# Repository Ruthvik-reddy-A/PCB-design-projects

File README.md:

# 🔧 PCB Design Projects

This combined repository contains self-contained folders for each individual project, along with complete schematics, PCB layouts, documentation, and source files where applicable. It serves both as a personal portfolio and an open-source contribution to the maker and engineering community.

---

## 📁 Projects Overview

### 1. [📦 Breadboard Power Supply](./Breadboard-Power-Supply)

A compact, dual-voltage regulated power supply designed to power breadboard circuits. Ideal for prototyping and educational use.

**Key Features:**
- Outputs: 3.3V and 5V regulated
- Power input via USB or 9V barrel jack
- On/off toggle switches and status LEDs

---

### 2. [📦 MCU Datalogger with Built-in 512K EEPROM](./MCU-Datalogger-With-Built-In-512K-EEPROM)

A microcontroller-based data logger that logs sensor or serial data to a 512KB external EEPROM.

**Key Features:**
- ATmega328P-based MCU
- I²C EEPROM (24LC512)
- Power supply filtering and decoupling
- Compatible with UART, I²C sensors or serial interfaces

---

### 3. [📦 Tiny Solar Power Supply](./Tiny-Solar-Power-Supply)

A miniature solar energy harvesting module capable of charging a Li-ion battery and regulating output to power IoT devices or small loads.

**Key Features:**
- Solar input with MPPT (if supported by controller)
- Li-ion battery charging via TP4056
- Regulated 3.3V/5V output
- Compact PCB layout

---

### 4. [📦 LED Torch](./LED%20Torch)  
A compact, battery-powered LED torch circuit using minimal components. Designed for efficiency, simplicity, and portability, this project is ideal for learning basic electronics or building a low-cost flashlight.

---

### 5. [📡 GPS + GSM Tracker with EEPROM Logging](https://github.com/Ruthvik-reddy-A/PCB-design-projects/tree/main/GPS%20%2B%20GSM%20Tracker%20with%20EEPROM%20Logging)
A compact, ESP32-S3-based IoT tracker that logs GPS data locally and transmits position via GSM. Ideal for asset tracking, vehicle monitoring, and offline location logging in remote or mobile environments.

**Key Features:**
- Microcontroller: ESP32-S3-WROOM-1 with Wi-Fi + BLE
- GPS Module: NEO-8Q for real-time latitude/longitude tracking
- GSM Module: SIM800C for SMS or GPRS-based data transmission
- EEPROM: I²C-based 24LC256 for offline GPS data logging

**Power Supply:**
- Input: 3.7V LiPo battery
- Charging: TP4056 module with battery protection
- Regulation: AMS1117-3.3 for ESP32, Boost converter for SIM800C

**Communication:**
- 3× UARTs for GPS, GSM, and FTDI debugging
- 1× I²C for EEPROM and future expansion
- SPI pins available for SD card or display

**Indicators:**
- LED status for power, charging, and ESP32 boot
- Power control switch for full system on/off

---

## 📦 Folder Structure

Each folder includes:
- ✅ `README.md`
- ✅ `.gitignore`
- ✅ Schematics, PCB Layouts
- ✅ Bill of Materials (BOM)
- ✅ Gerber & Drill files
- ✅ Source code (if applicable)

---

## 🙌 Contributions

Feel free to fork or suggest improvements. Each project is self-contained and documented to allow easy reuse or remixing.

---

## 🔗 Related Repositories (Now Archived/Private)

These projects were originally developed in individual repositories:
- `PCB--BB-PowerSupply`
- `PCB--MCU-Datalogger`
- `PCB--Tiny-Solar-Power-Supply`

They have been combined here for easier access and long-term maintenance.

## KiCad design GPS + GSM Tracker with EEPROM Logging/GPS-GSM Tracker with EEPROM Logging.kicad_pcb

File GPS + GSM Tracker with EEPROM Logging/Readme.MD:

# 📡 IoT GPS-GSM Tracker with ESP32-S3 + EEPROM Logging

An ESP32-S3 based IoT hardware project for **location tracking** using a **GPS module (NEO-8Q)**, with real-time updates via **GSM (SIM800C)** and local data logging using an **I²C EEPROM (AT24C256)**. Power is managed via a **3.7V LiPo battery**, **TP4056 charger**, and **MT3608 boost converter**.

---

## 🧩 Features

- 📍 Real-time GPS tracking (NEO-8Q)
- 📡 GSM-based data transmission (SIM800C)
- 📦 EEPROM logging (AT24C256) for offline storage
- 🔋 Battery-powered with charging via TP4056
- ⚡ Boost conversion to 4.1V using MT3608
- 🧠 Controlled by ESP32-S3 (WROOM-1)

---

## 🔋 Power Architecture

| Source         | Voltage | Connected To     |
|----------------|---------|------------------|
| 3.7V LiPo      | 3.0–4.2V | TP4056 + MT3608  |
| TP4056 OUT     | 3.7V     | MT3608 Input     |
| MT3608 OUT     | 4.1V     | SIM800C VBAT     |
| LDO Regulator  | 3.3V     | ESP32, EEPROM, GPS |

---

## 🔌 Module Connections

### ESP32-S3 ↔ GPS (NEO-8Q)
| ESP32 Pin | GPS Pin |
|-----------|---------|
| RX2       | TX      |
| TX2       | RX      |
| 3.3V      | VCC     |
| GND       | GND     |

### ESP32-S3 ↔ SIM800C (via TXS0108E level shifter)
| ESP32 Pin | SIM800C Pin |
|-----------|-------------|
| TX1       | RX          |
| RX1       | TX          |
| GND       | GND         |
| OE (TXS)  | 3.3V        |

### ESP32-S3 ↔ EEPROM (AT24C256)
| ESP32 Pin | EEPROM Pin |
|-----------|-------------|
| GPIO21    | SDA         |
| GPIO22    | SCL         |
| 3.3V      | VCC         |
| GND       | GND         |

---

## 📐 Schematic Overview

📎 The following components are included:
- ESP32-S3-WROOM-1
- NEO-8Q GPS module (passive antenna)
- SIM800C GSM module with SMA antenna
- MT3608 boost converter
- TP4056 LiPo charger module
- AT24C256 EEPROM (I²C)
- Status LEDs and EN/BOOT buttons

📷 *[Include schematic image or KiCad 3D render here]*

---

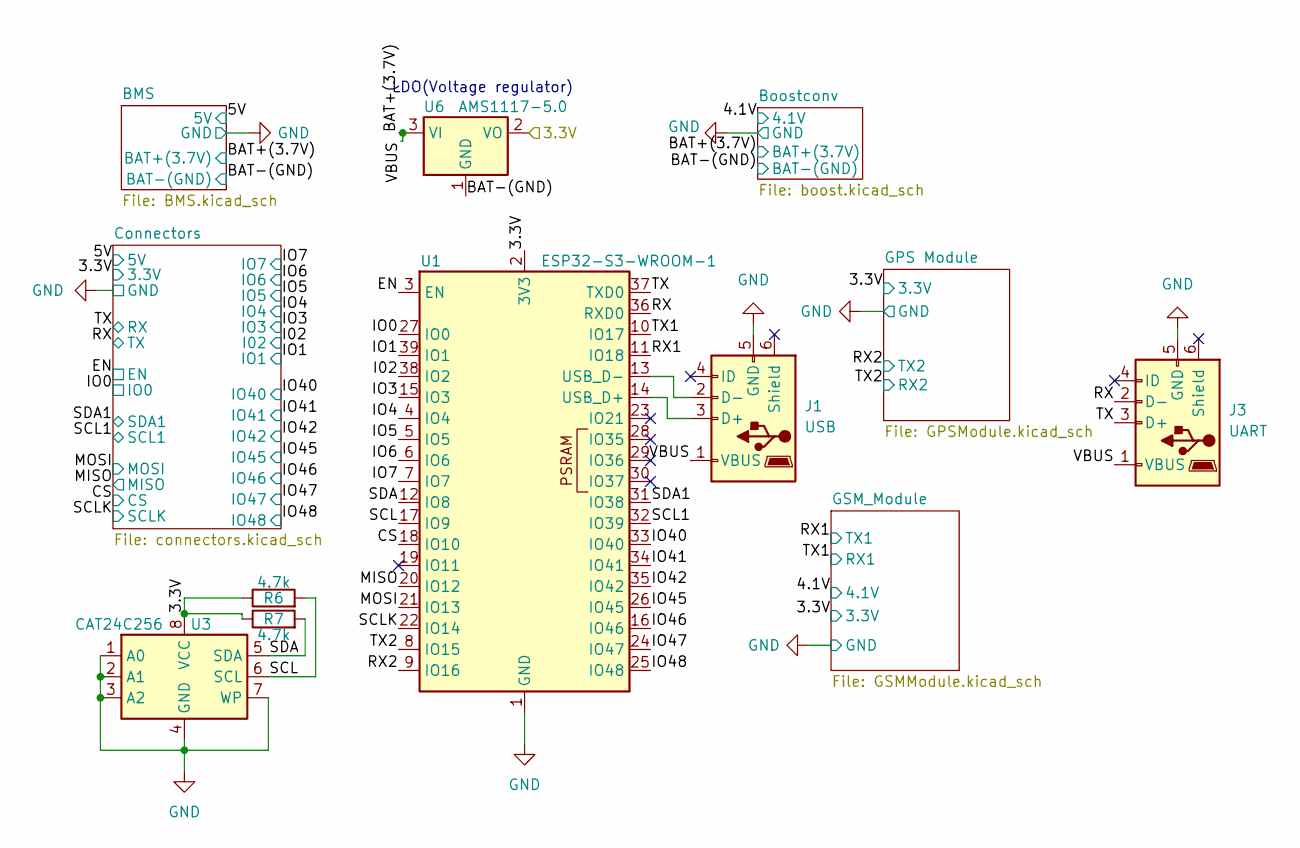
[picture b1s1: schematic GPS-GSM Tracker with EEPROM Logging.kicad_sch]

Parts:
J1: USB; USB_Micro-AB_Molex_47590-0001
J3: UART; USB_Micro-AB_Molex_47590-0001
R6, R7: 4.7k; R_0805_2012Metric
U1: ESP32-S3-WROOM-1
U3: CAT24C256; SOIC-8_3.9x4.9mm_P1.27mm
U6: AMS1117-5.0; SOT-223-3_TabPin2

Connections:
/3.3V: R6.1, R7.1, U1.2 (3V3), U3.8 (VCC), U6.2 (VO); also elsewhere on the board
/BAT+(3.7V): J1.1 (VBUS), J3.1 (VBUS), U6.3 (VI); also elsewhere on the board
/CS: U1.18 (IO10); also elsewhere on the board
/EN: U1.3 (EN); also elsewhere on the board
/I02: U1.38 (IO2); also elsewhere on the board
/IO0: U1.27 (IO0); also elsewhere on the board
/IO1: U1.39 (IO1); also elsewhere on the board
/IO3: U1.15 (IO3); also elsewhere on the board
/IO4: U1.4 (IO4); also elsewhere on the board
/IO5: U1.5 (IO5); also elsewhere on the board
/IO6: U1.6 (IO6); also elsewhere on the board
/IO7: U1.7 (IO7); also elsewhere on the board
/IO40: U1.33 (IO40); also elsewhere on the board
/IO41: U1.34 (IO41); also elsewhere on the board
/IO42: U1.35 (IO42); also elsewhere on the board
/IO45: U1.26 (IO45); also elsewhere on the board
/IO46: U1.16 (IO46); also elsewhere on the board
/IO47: U1.24 (IO47); also elsewhere on the board
/IO48: U1.25 (IO48); also elsewhere on the board
/MISO: U1.20 (IO12); also elsewhere on the board
/MOSI: U1.21 (IO13); also elsewhere on the board
/RX: J3.2 (D-), U1.36 (RXD0); also elsewhere on the board
/RX1: U1.11 (IO18); also elsewhere on the board
/RX2: U1.9 (IO16); also elsewhere on the board
/SCL: R6.2, U1.17 (IO9), U3.6 (SCL)
/SCL1: U1.32 (IO39); also elsewhere on the board
/SCLK: U1.22 (IO14); also elsewhere on the board
/SDA: R7.2, U1.12 (IO8), U3.5 (SDA)
/SDA1: U1.31 (IO38); also elsewhere on the board
/TX: J3.3 (D+), U1.37 (TXD0); also elsewhere on the board
/TX1: U1.10 (IO17); also elsewhere on the board
/TX2: U1.8 (IO15); also elsewhere on the board
GND: J1.5 (GND), J3.5 (GND), U1.1 (GND), U1.40 (GND), U1.41 (GND), U3.1 (A0), U3.2 (A1), U3.3 (A2), U3.4 (GND), U3.7 (WP), U6.1 (GND); also elsewhere on the board
unnamed 41: J1.3 (D+), U1.14 (USB_D+); also elsewhere on the board
unnamed 42: J1.2 (D-), U1.13 (USB_D-); also elsewhere on the board

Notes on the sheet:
LDO(Voltage regulator)

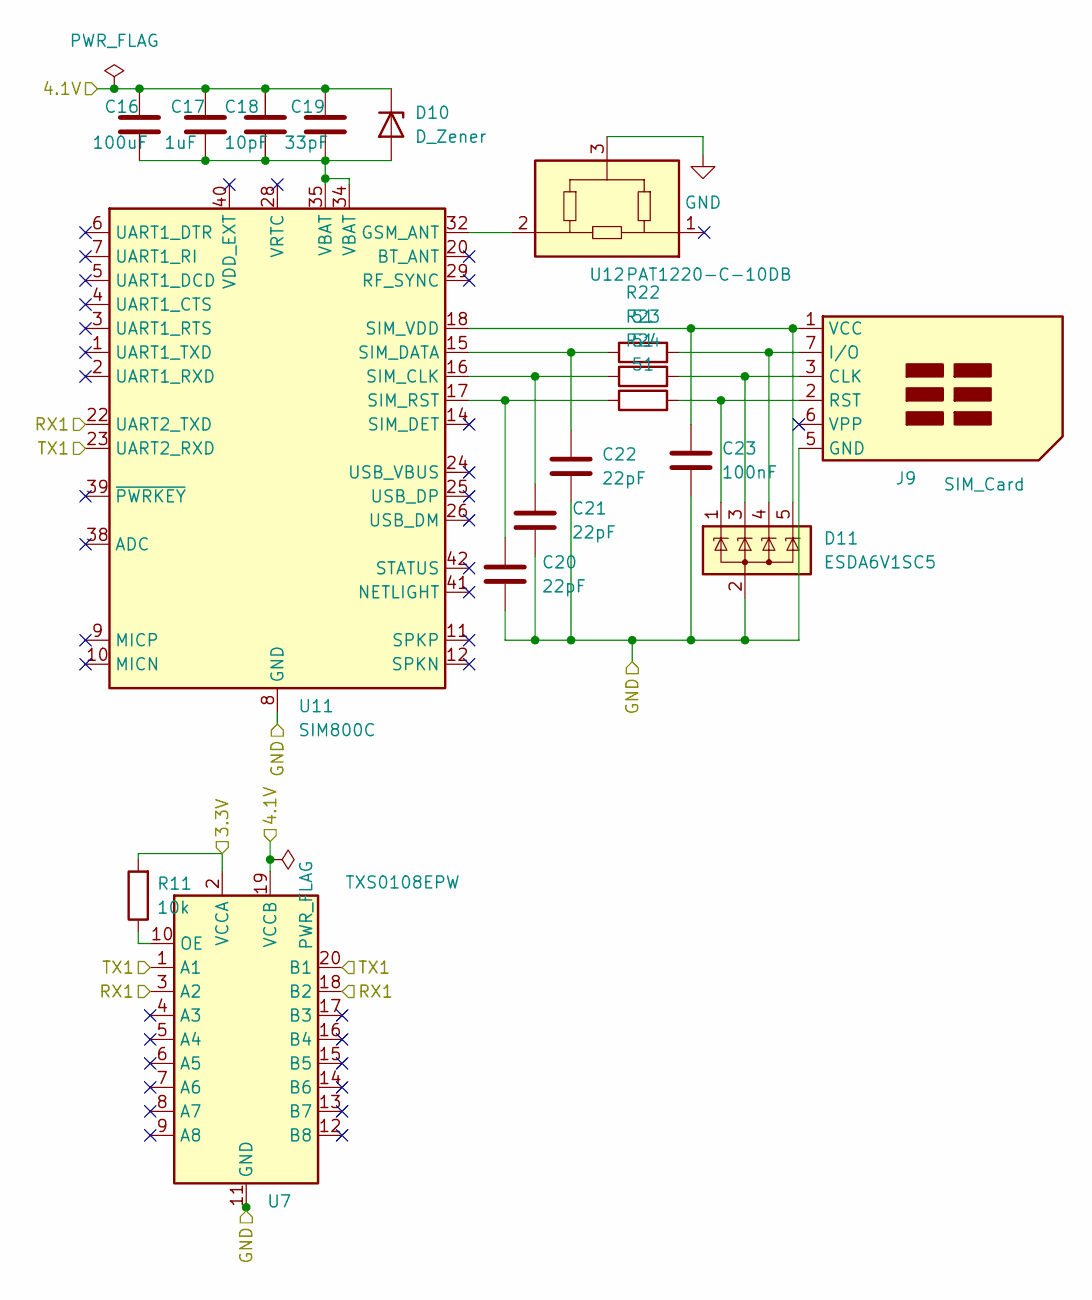
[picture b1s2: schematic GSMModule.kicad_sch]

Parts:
C16: 100uF; C_0805_2012Metric
C17: 1uF; C_0805_2012Metric
C18: 10pF; C_0805_2012Metric
C19: 33pF; C_0805_2012Metric
C20, C21, C22: 22pF; C_0805_2012Metric
C23: 100nF; C_0805_2012Metric
D10: D_Zener; D_SOD-323F
D11: ESDA6V1SC5; SOT-23-5
J9: SIM_Card; nanoSIM_GCT_SIM8060-6-0-14-00
R11: 10k; R_0805_2012Metric
R22, R23, R24: 51; R_0805_2012Metric
U7: TXS0108EPW; TSSOP-20_4.4x6.5mm_P0.65mm
U11: SIM800C; SIMCom_SIM800C
U12: PAT1220-C-10DB; RF_Attenuator_Susumu_PAT1220

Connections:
/3.3V: R11.2, U7.2 (VCCA); also elsewhere on the board
/RX1: U7.1 (A1), U7.20 (B1), U11.23 (UART2_RXD); also elsewhere on the board
/TX1: U7.3 (A2), U7.18 (B2), U11.22 (UART2_TXD); also elsewhere on the board
GND: C20.2, C21.2, C22.2, C23.2, D11.2 (A), J9.5 (GND), U7.11 (GND), U11.8 (GND), U11.13 (GND), U11.19 (GND), U11.21 (GND), U11.27 (GND), U11.30 (GND), U11.31 (GND), U11.33 (GND), U11.36 (GND), U11.37 (GND), U12.3; also elsewhere on the board
unnamed: C16.2, C17.2, C18.2, C19.2, D10.2 (A), U11.34 (VBAT), U11.35 (VBAT)
unnamed: D11.3 (K), J9.3 (CLK), R23.2
unnamed: D11.4 (K), J9.7 (I/O), R22.2
unnamed: D11.1 (K), J9.2 (RST), R24.2
unnamed: C23.1, D11.5 (K), J9.1 (VCC), U11.18 (SIM_VDD)
unnamed: R11.1, U7.10 (OE)
unnamed: U11.32 (GSM_ANT), U12.2
unnamed: C21.1, R23.1, U11.16 (SIM_CLK)
unnamed: C22.1, R22.1, U11.15 (SIM_DATA)
unnamed: C20.1, R24.1, U11.17 (SIM_RST)
PWR_FLAG: C16.1, C17.1, C18.1, C19.1, D10.1 (K), U7.19 (VCCB); also elsewhere on the board

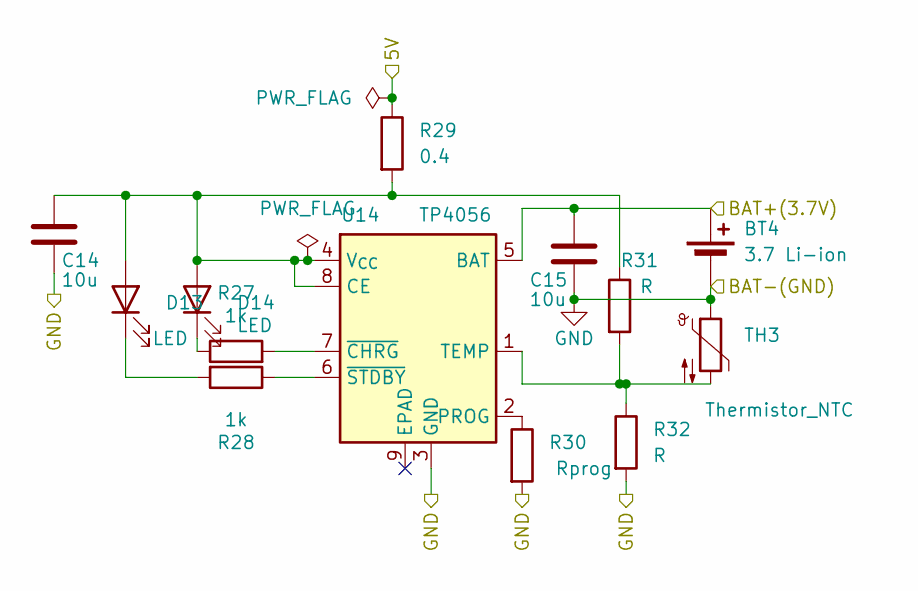
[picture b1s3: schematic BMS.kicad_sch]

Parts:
BT4: 3.7 Li-ion; BatteryHolder_Keystone_1042_1x18650
C14, C15: 10u; C_0805_2012Metric
D13, D14: LED; LED_0805_2012Metric
R27, R28: 1k; R_0805_2012Metric
R29: 0.4; R_0805_2012Metric
R30: Rprog; R_0805_2012Metric
R31, R32: R; R_0805_2012Metric
TH3: Thermistor_NTC; Heraeus_TO-92-2
U14: TP4056; SOIC-8-1EP_3.9x4.9mm_P1.27mm_EP2.41x3.3mm_ThermalVias

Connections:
/5V: R29.1; also elsewhere on the board
/BAT+(3.7V): BT4.1 (+), C15.1, U14.5 (BAT); also elsewhere on the board
GND: BT4.2 (-), C14.2, C15.2, R30.2, R32.2, TH3.1, U14.3 (GND); also elsewhere on the board
unnamed: C14.1, D13.2 (A), D14.2 (A), R29.2, R31.1, U14.4 (V_{CC}), U14.8 (CE)
unnamed: D13.1 (K), R28.2
unnamed: D14.1 (K), R27.1
unnamed: R30.1, U14.2 (PROG)
unnamed: R31.2, R32.1, TH3.2, U14.1 (TEMP)
unnamed: R27.2, U14.7 (~CHRG)
unnamed: R28.1, U14.6 (~STDBY)

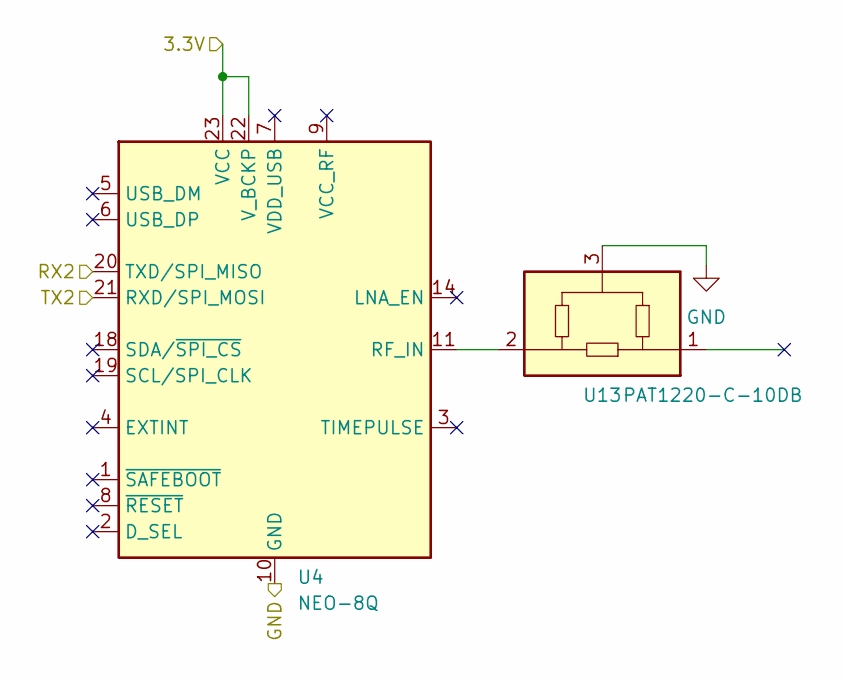
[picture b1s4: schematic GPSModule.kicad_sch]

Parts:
U4: NEO-8Q; ublox_NEO
U13: PAT1220-C-10DB; RF_Attenuator_Susumu_PAT1220

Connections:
/3.3V: U4.22 (V_BCKP), U4.23 (VCC); also elsewhere on the board
/RX2: U4.21 (RXD/SPI_MOSI); also elsewhere on the board
/TX2: U4.20 (TXD/SPI_MISO); also elsewhere on the board
GND: U4.10 (GND), U4.12 (GND), U4.13 (GND), U4.24 (GND), U13.3; also elsewhere on the board
unnamed: U4.11 (RF_IN), U13.2

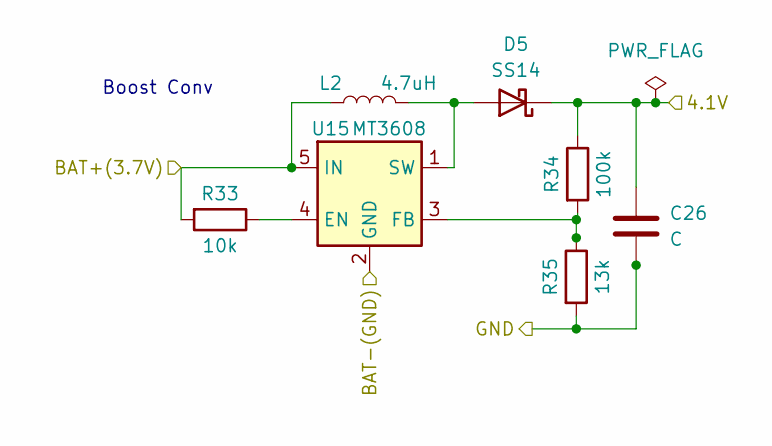
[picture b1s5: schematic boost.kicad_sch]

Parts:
C26: C; C_0805_2012Metric
D5: SS14; D_SMA
L2: 4.7uH; L_0805_2012Metric
R33: 10k; R_0805_2012Metric
R34: 100k; R_0805_2012Metric
R35: 13k; R_0805_2012Metric
U15: MT3608; SOT-23-6

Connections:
/BAT+(3.7V): L2.1, R33.2, U15.5 (IN); also elsewhere on the board
GND: C26.1, R35.2, U15.2 (GND); also elsewhere on the board
unnamed: D5.2 (A), L2.2, U15.1 (SW)
unnamed: R33.1, U15.4 (EN)
unnamed: R34.2, R35.1, U15.3 (FB)
PWR_FLAG: C26.2, D5.1 (K), R34.1; also elsewhere on the board

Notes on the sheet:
Boost Conv

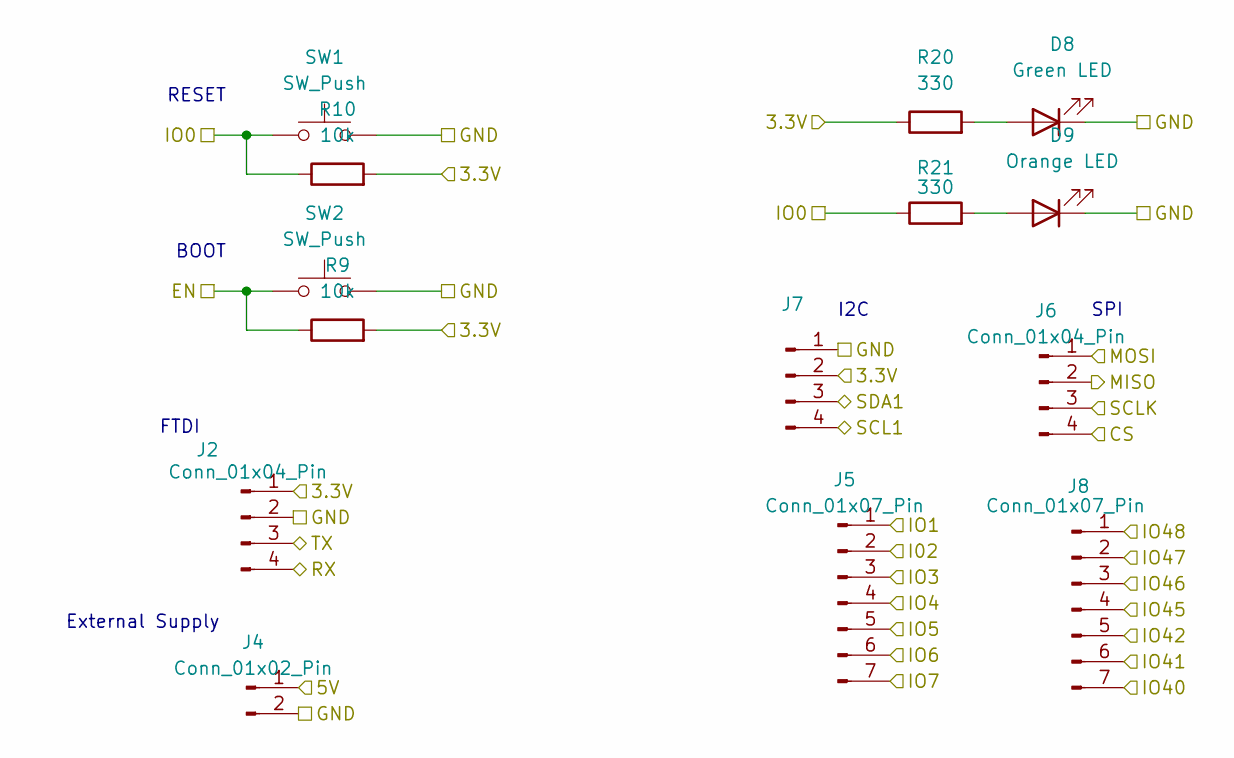
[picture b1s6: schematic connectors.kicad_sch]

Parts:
D8: Green LED; LED_0805_2012Metric
D9: Orange LED; LED_0805_2012Metric
J2, J6, J7: Conn_01x04_Pin; Molex_KK-254_AE-6410-04A_1x04_P2.54mm_Vertical
J4: Conn_01x02_Pin; Molex_KK-254_AE-6410-02A_1x02_P2.54mm_Vertical
J5, J8: Conn_01x07_Pin; Molex_KK-254_AE-6410-07A_1x07_P2.54mm_Vertical
R9, R10: 10k; R_0805_2012Metric
R20, R21: 330; R_0805_2012Metric
SW1, SW2: SW_Push; SW_PUSH_6mm_H4.3mm

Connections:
/3.3V: J2.1, J7.2, R9.2, R10.2, R20.1; also elsewhere on the board
/5V: J4.1; also elsewhere on the board
/CS: J6.4; also elsewhere on the board
/EN: R9.1, SW2.1; also elsewhere on the board
/I02: J5.2; also elsewhere on the board
/IO0: R10.1, R21.1, SW1.1; also elsewhere on the board
/IO1: J5.1; also elsewhere on the board
/IO3: J5.3; also elsewhere on the board
/IO4: J5.4; also elsewhere on the board
/IO5: J5.5; also elsewhere on the board
/IO6: J5.6; also elsewhere on the board
/IO7: J5.7; also elsewhere on the board
/IO40: J8.7; also elsewhere on the board
/IO41: J8.6; also elsewhere on the board
/IO42: J8.5; also elsewhere on the board
/IO45: J8.4; also elsewhere on the board
/IO46: J8.3; also elsewhere on the board
/IO47: J8.2; also elsewhere on the board
/IO48: J8.1; also elsewhere on the board
/MISO: J6.2; also elsewhere on the board
/MOSI: J6.1; also elsewhere on the board
/RX: J2.3; also elsewhere on the board
/SCL1: J7.4; also elsewhere on the board
/SCLK: J6.3; also elsewhere on the board
/SDA1: J7.3; also elsewhere on the board
/TX: J2.4; also elsewhere on the board
GND: D8.1 (K), D9.1 (K), J2.2, J4.2, J7.1, SW1.2, SW2.2; also elsewhere on the board
unnamed: D8.2 (A), R20.2
unnamed: D9.2 (A), R21.2

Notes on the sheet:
External Supply
I2C
FTDI
BOOT
SPI
RESET

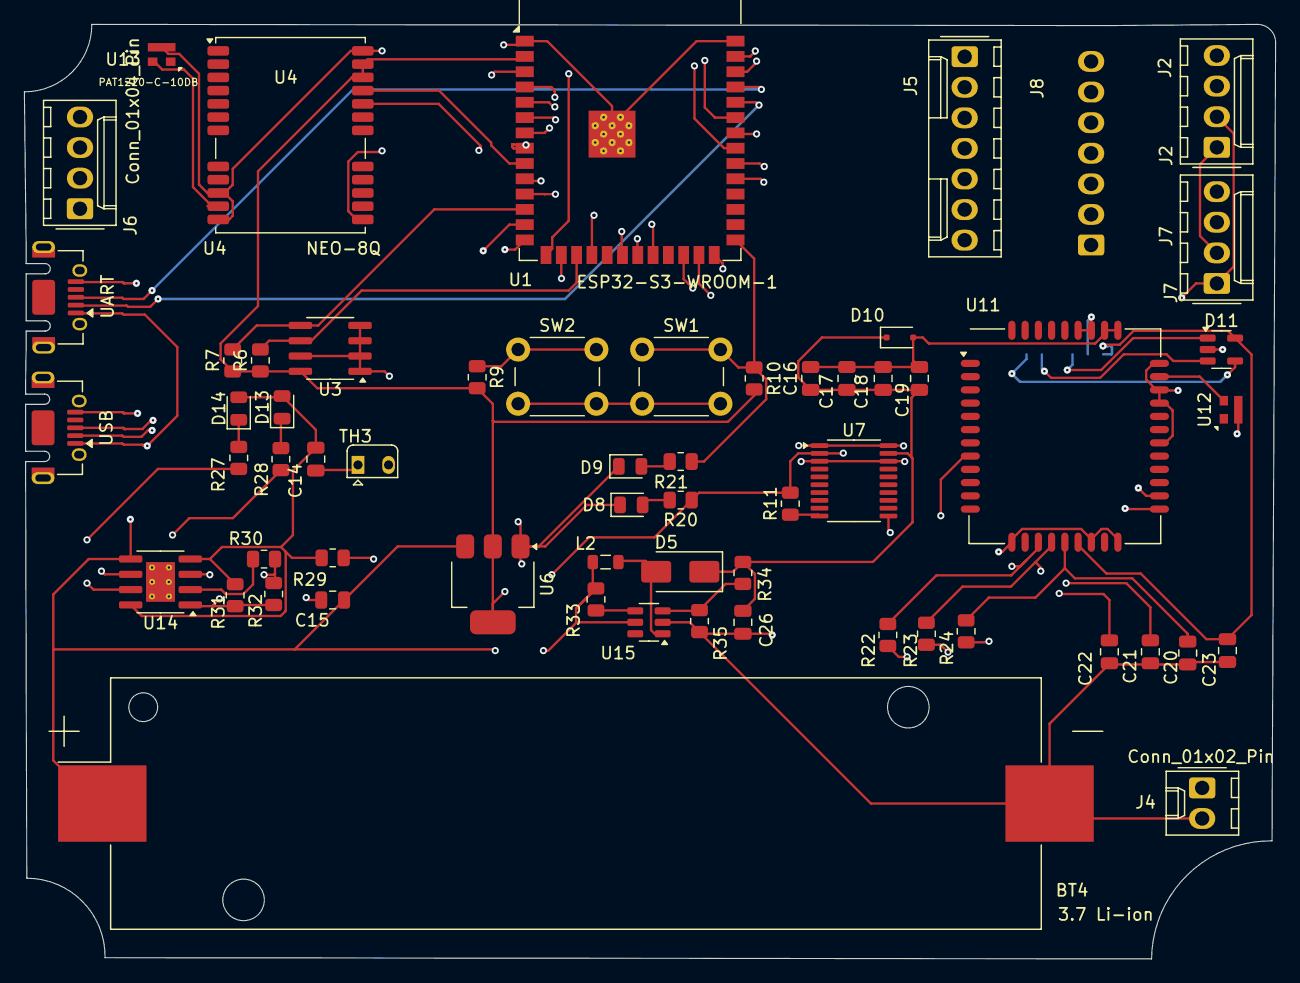
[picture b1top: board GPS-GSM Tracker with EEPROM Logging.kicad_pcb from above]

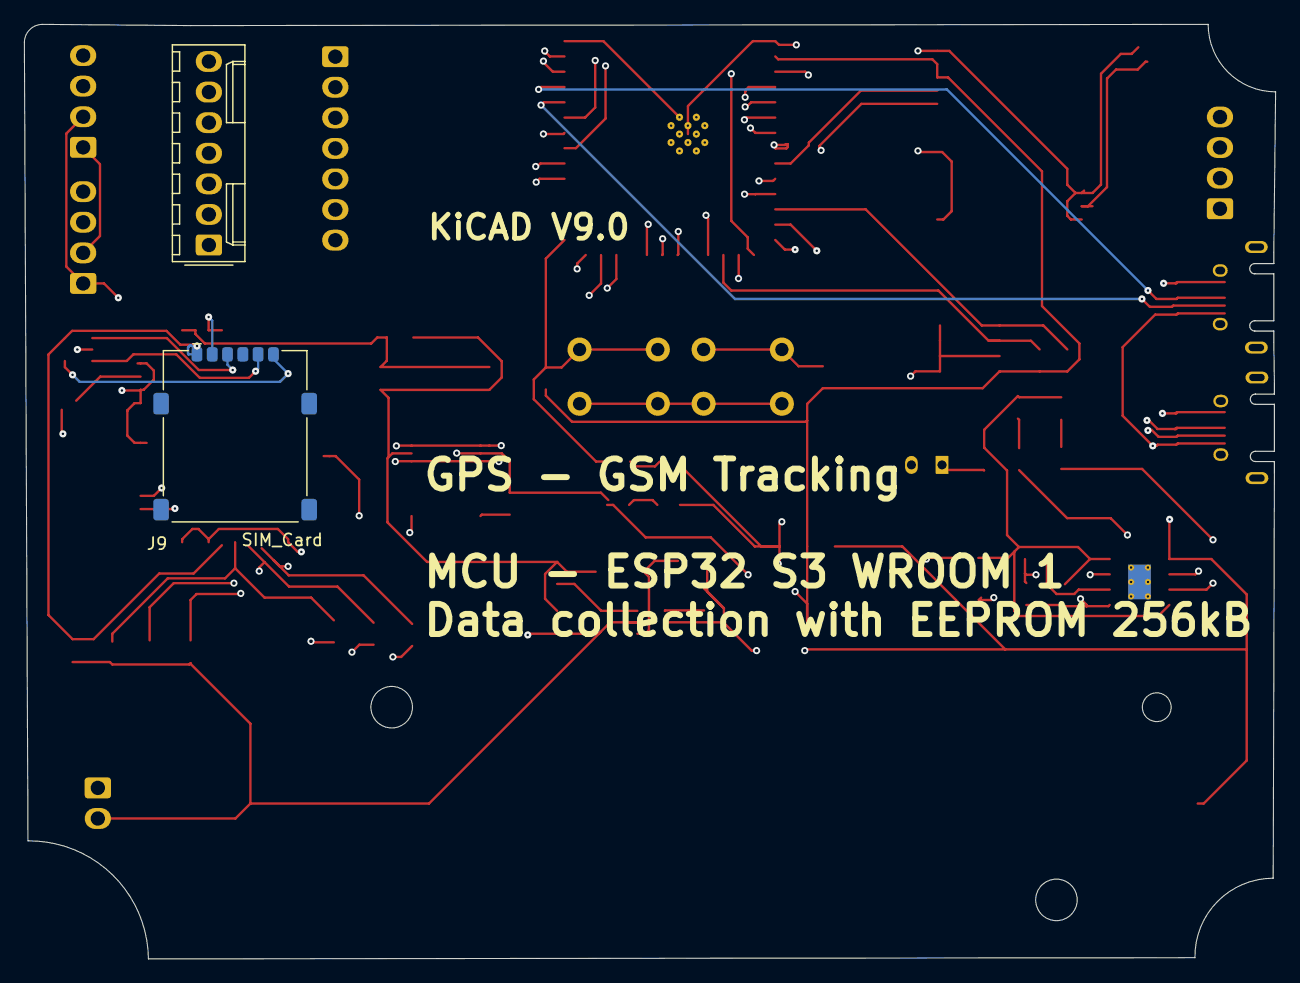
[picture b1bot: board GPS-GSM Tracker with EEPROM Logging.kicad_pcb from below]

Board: 4 copper layers, 103.9 x 77.6 mm, 61 parts (2 on the bottom side), 60 nets.

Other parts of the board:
UART: UART; USB_Micro-AB_Molex_47590-0001
USB: USB; USB_Micro-AB_Molex_47590-0001

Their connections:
/BAT+(3.7V): UART.1 (VBUS), USB.1 (VBUS); also elsewhere on the board
/RX: UART.2 (D-); also elsewhere on the board
/TX: UART.3 (D+); also elsewhere on the board
GND: UART.5 (GND), USB.5 (GND); also elsewhere on the board
unnamed 41: USB.3 (D+); also elsewhere on the board
unnamed 42: USB.2 (D-); also elsewhere on the board

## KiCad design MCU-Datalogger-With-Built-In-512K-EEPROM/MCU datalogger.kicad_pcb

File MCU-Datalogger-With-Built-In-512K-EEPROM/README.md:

# 🧾 MCU Data Logger – PCB Design

This repository contains the complete PCB design files and documentation for a microcontroller-based data logger with 512KB external EEPROM. The system is designed to log sensor data and store it in non-volatile memory, making it ideal for long-term, standalone data acquisition applications.

---

🔧 Designed using: KiCad 

📐 PCB Type: 2-layer, through-hole/SMD hybrid

---

## 🔋 Key Features
* Microcontroller-based core (ATmega328P / STM32 / ESP32)
* 512KB I²C EEPROM (e.g., 24LC512) for data storage
* Optional RTC (DS3231) for timestamped logging
* UART/USB interface for data extraction
* Breadboard-compatible or standalone PCB footprint
* Power input: USB / 5V header / Li-Ion with LDO
---

## 🔧 Hardware Block Diagram

## 🖼️ PCB Preview
Top View of the PCB:

Back View (if applicable):

---

## 📐 Pinouts & Interfaces

| Interface | Purpose               | Pin(s)            |
| --------- | --------------------- | ----------------- |
| I²C       | EEPROM, RTC           | SDA, SCL          |
| UART      | Serial communication  | TX, RX            |
| Power     | +5V / GND / Battery   | VIN, GND          |
| Sensor    | Analog/Digital inputs | A0, A1, D2, D3... |

---

## 📥 Data Logging Behavior
* Data sampled every X seconds
* Stored in EEPROM in binary or CSV-friendly format
* Memory managed using circular buffer logic
* Data dump via UART/USB when connected to host

---

## 🛠️ Fabrication & Assembly
* Use the included Gerber files (/gerbers) for fabrication
* Reference BOM (/bom.csv) for components
* Optionally reflow or hand-solder depending on design

---

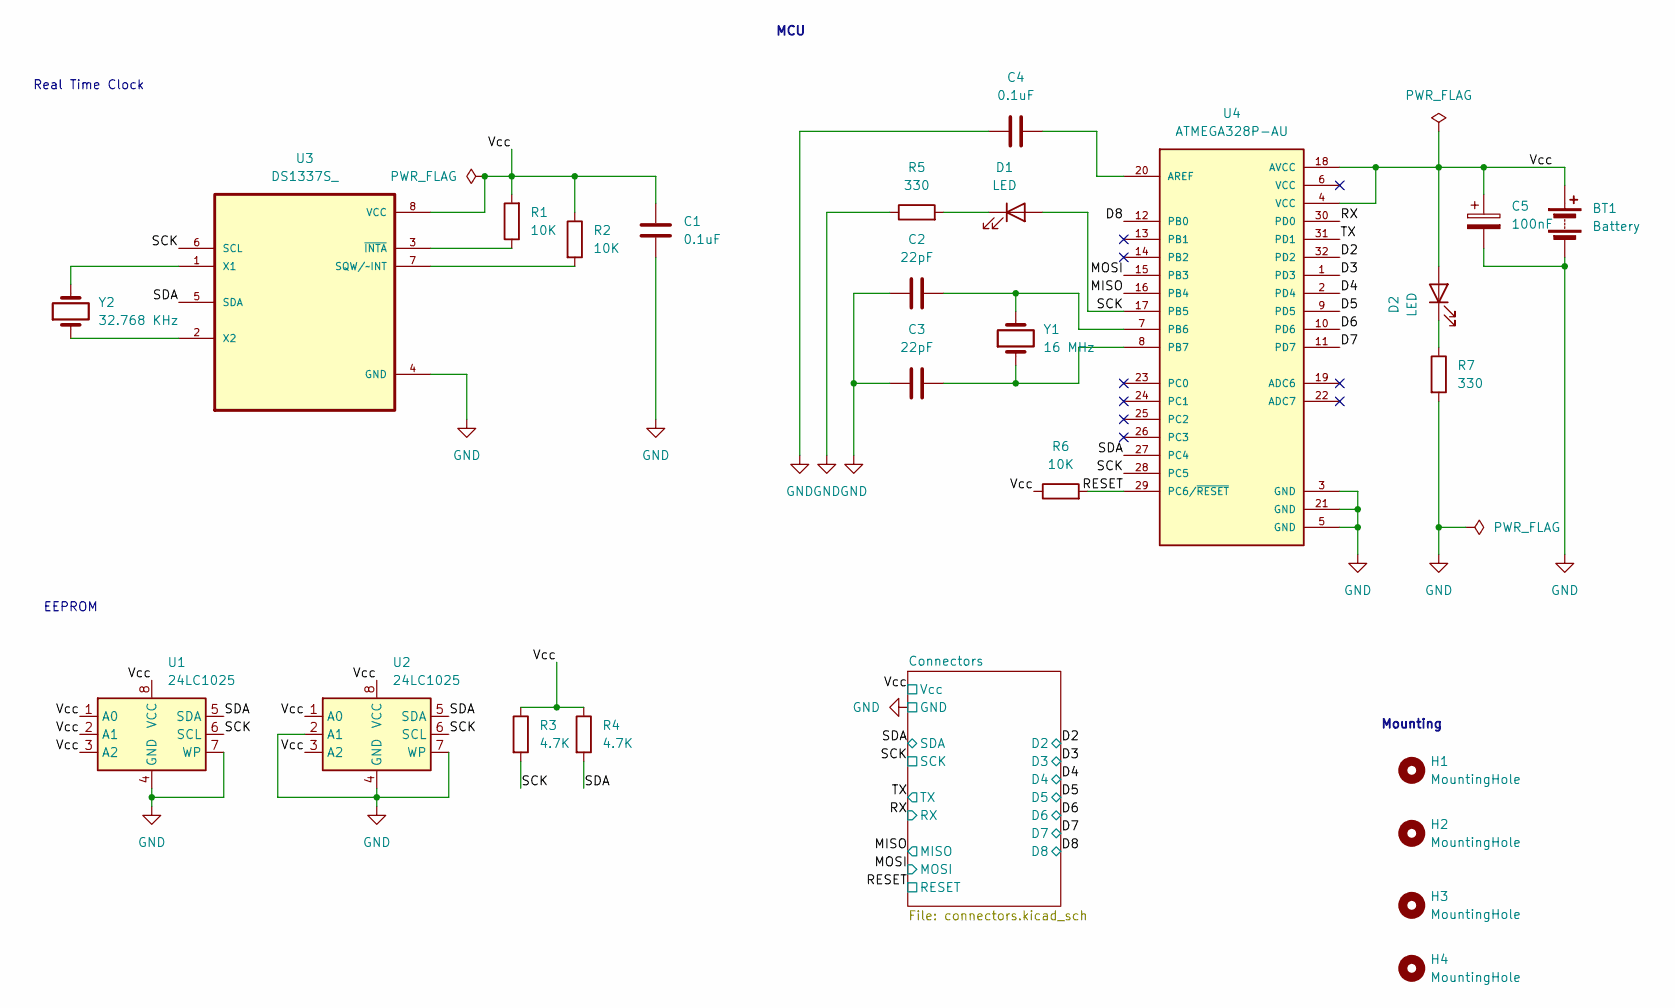
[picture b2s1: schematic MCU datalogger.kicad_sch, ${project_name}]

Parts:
BT1: Battery; PinHeader_1x02_P2.54mm_Vertical
C1, C4: 0.1uF; C_0805_2012Metric
C2, C3: 22pF; C_0805_2012Metric
C5: 100nF; C_0805_2012Metric
D1, D2: LED; LED_0805_2012Metric
H1, H2, H3, H4: MountingHole; MountingHole_2.1mm
R1, R2, R6: 10K; R_0805_2012Metric
R3, R4: 4.7K; R_0805_2012Metric
R5, R7: 330; R_0805_2012Metric
U1, U2: 24LC1025; SOIC-8_5.3x5.3mm_P1.27mm
U3: DS1337S_; SOIC127P600X175-8N
U4: ATMEGA328P-AU; QFP80P900X900X120-32N; PARTREV 8271A
Y1: 16 MHz; Crystal_SMD_5032-2Pin_5.0x3.2mm_HandSoldering
Y2: 32.768 KHz; Crystal_SMD_5032-2Pin_5.0x3.2mm_HandSoldering

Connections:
/D2: U4.32 (PD2); also elsewhere on the board
/D3: U4.1 (PD3); also elsewhere on the board
/D4: U4.2 (PD4); also elsewhere on the board
/D5: U4.9 (PD5); also elsewhere on the board
/D6: U4.10 (PD6); also elsewhere on the board
/D7: U4.11 (PD7); also elsewhere on the board
/D8: U4.12 (PB0); also elsewhere on the board
/MISO: U4.16 (PB4); also elsewhere on the board
/MOSI: U4.15 (PB3); also elsewhere on the board
/RESET: R6.2, U4.29 (PC6/~RESET); also elsewhere on the board
/RX: U4.30 (PD0); also elsewhere on the board
/SCK: D1.2 (A), R3.2, U1.6 (SCL), U2.6 (SCL), U3.6 (SCL), U4.17 (PB5), U4.28 (PC5); also elsewhere on the board
/SDA: R4.2, U1.5 (SDA), U2.5 (SDA), U3.5 (SDA), U4.27 (PC4); also elsewhere on the board
/TX: U4.31 (PD1); also elsewhere on the board
/Vcc: BT1.1 (+), C1.1, C5.1, D2.2 (A), R1.2, R2.1, R3.1, R4.1, R6.1, U1.1 (A0), U1.2 (A1), U1.3 (A2), U1.8 (VCC), U2.1 (A0), U2.3 (A2), U2.8 (VCC), U3.8 (VCC), U4.4 (VCC), U4.18 (AVCC); also elsewhere on the board
GND: BT1.2 (-), C1.2, C2.1, C3.1, C4.1, C5.2, R5.1, R7.2, U1.4 (GND), U1.7 (WP), U2.2 (A1), U2.4 (GND), U2.7 (WP), U3.4 (GND), U4.3 (GND), U4.5 (GND), U4.21 (GND); also elsewhere on the board
unnamed: D1.1 (K), R5.2
unnamed: D2.1 (K), R7.1
unnamed: R2.2, U3.7 (SQW/~INT)
unnamed: U3.1 (X1), Y2.2
unnamed: U3.2 (X2), Y2.1
unnamed: R1.1, U3.3 (~INTA)
unnamed: C4.2, U4.20 (AREF)
unnamed: C2.2, U4.7 (PB6), Y1.2
unnamed: C3.2, U4.8 (PB7), Y1.1

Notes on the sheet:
Real Time Clock
Mounting
MCU
EEPROM

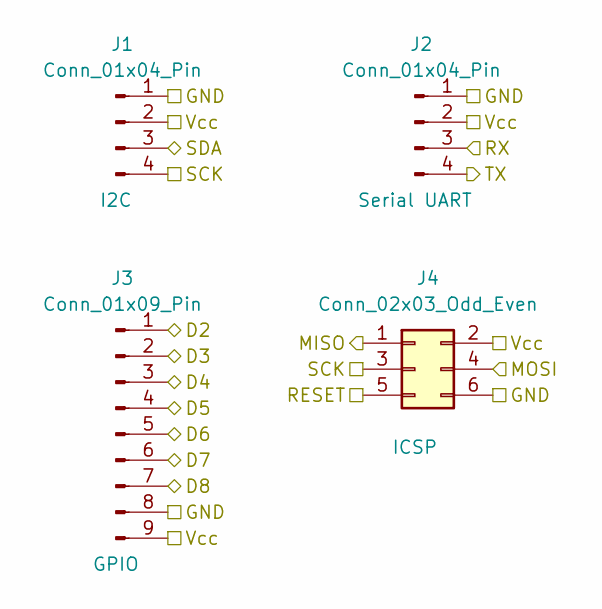
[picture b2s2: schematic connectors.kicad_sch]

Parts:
J1, J2: Conn_01x04_Pin; PinHeader_1x04_P2.54mm_Vertical
J3: Conn_01x09_Pin; PinHeader_1x09_P2.54mm_Vertical
J4: Conn_02x03_Odd_Even; PinHeader_2x03_P2.54mm_Vertical

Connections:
/D2: J3.1; also elsewhere on the board
/D3: J3.2; also elsewhere on the board
/D4: J3.3; also elsewhere on the board
/D5: J3.4; also elsewhere on the board
/D6: J3.5; also elsewhere on the board
/D7: J3.6; also elsewhere on the board
/D8: J3.7; also elsewhere on the board
/MISO: J4.1; also elsewhere on the board
/MOSI: J4.4; also elsewhere on the board
/RESET: J4.5; also elsewhere on the board
/RX: J2.3; also elsewhere on the board
/SCK: J1.4, J4.3; also elsewhere on the board
/SDA: J1.3; also elsewhere on the board
/TX: J2.4; also elsewhere on the board
/Vcc: J1.2, J2.2, J3.9, J4.2; also elsewhere on the board
GND: J1.1, J2.1, J3.8, J4.6; also elsewhere on the board

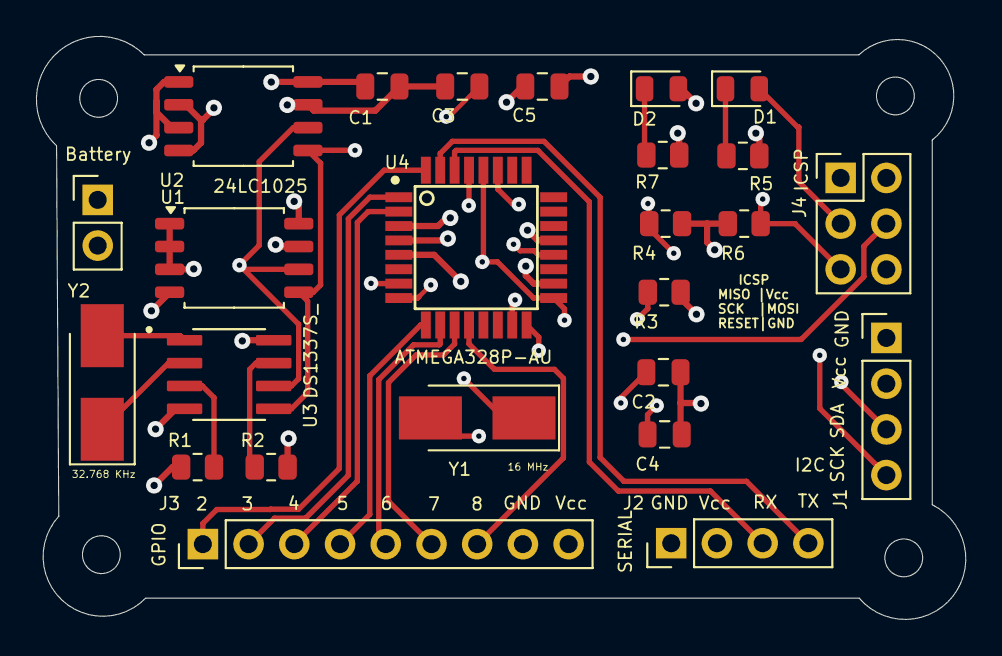
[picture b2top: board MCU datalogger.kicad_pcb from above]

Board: 4 copper layers, 51.6 x 32.4 mm, 29 parts (0 on the bottom side), 25 nets.

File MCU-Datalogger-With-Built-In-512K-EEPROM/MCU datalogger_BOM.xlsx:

Id | Designator | Footprint | Quantity | Designation | Supplier and ref | Column1 | _1
1 | BT1 | PinHeader_1x02_P2.54mm_Vertical | 1 | Battery
2 | R4,R3 | R_0805_2012Metric | 2 | 4.7K
3 | J1,J2 | PinHeader_1x04_P2.54mm_Vertical | 2 | Conn_01x04_Pin
4 | J4 | PinHeader_2x03_P2.54mm_Vertical | 1 | Conn_02x03_Odd_Even
5 | D2,D1 | LED_0805_2012Metric | 2 | LED
6 | C1,C4 | C_0805_2012Metric | 2 | 0.1uF
7 | Y1 | Crystal_SMD_5032-2Pin_5.0x3.2mm_HandSoldering | 1 | 16 MHz
8 | R5,R7 | R_0805_2012Metric | 2 | 330
9 | C3,C2 | C_0805_2012Metric | 2 | 22pF
10 | C5 | C_0805_2012Metric | 1 | 100nF
11 | U1,U2 | SOIC-8_5.3x5.3mm_P1.27mm | 2 | 24LC1025
12 | Y2 | Crystal_SMD_5032-2Pin_5.0x3.2mm_HandSoldering | 1 | 32.768 KHz
13 | R2,R1,R6 | R_0805_2012Metric | 3 | 10K
14 | J3 | PinHeader_1x09_P2.54mm_Vertical | 1 | Conn_01x09_Pin
15 | U4 | QFP80P900X900X120-32N | 1 | ATMEGA328P-AU
16 | U3 | SOIC127P600X175-8N | 1 | DS1337S_

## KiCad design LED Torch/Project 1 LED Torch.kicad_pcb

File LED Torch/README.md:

# 🔦 LED Torch Project

A simple, compact, and low-power LED torch circuit designed for basic lighting applications. This project demonstrates the use of common electronic components to build a reliable and reusable LED lighting system powered by batteries.

---

## 📸 Preview

 <!-- Replace with actual path if available -->

---

## 📸 Schematic

---

## ⚙️ Features

- ✅ Efficient LED driver using discrete components
- 🔋 Battery-powered (1.5V/3V/AA/AAA or coin cell based)
- 🔄 Optional on/off switch or push button
- 💡 Designed for white LED (or red/green/blue options)
- 🪛 Minimal component count for easy DIY assembly

---

## 🔧 Circuit Overview

This LED torch uses a simple boost converter or current-limiting resistor circuit depending on configuration. It lights up one or more LEDs from a low-voltage battery source, offering basic illumination.

Typical components used:
- Transistor (e.g. 2N2222 / BC547)
- White LED (3.0–3.3V forward voltage)
- Resistor for current control (100–470Ω)
- Power switch or jumper
- Battery holder for AA / AAA or coin cells

---

## 📋 Bill of Materials (BOM)

| Component     | Value / Part       | Description                         |
|---------------|--------------------|-------------------------------------|
| Q1            | 2N2222 / BC547      | NPN transistor                      |
| R1            | 100–470Ω            | LED current-limiting resistor       |
| LED1          | 5mm White LED       | Main torch light                    |
| S1            | SPST Switch / Jumper | Torch On/Off control                |
| Battery       | AA / AAA / Coin cell | Power source (1.5–3V)              |
| PCB           | Custom single-sided | Compact torch layout                |

---

## 🖥️ PCB Design

The PCB is compact and designed to fit inside a small torch enclosure or be mounted on a keychain or clip. It includes pads for the switch, LED, and battery holder.

> PCB layout, schematic, and Gerber files are included in the `/pcb/` folder.

---

## 🚀 Usage Instructions

1. Solder all components as per schematic
2. Insert battery and close the case
3. Toggle the switch to power the LED
4. For higher brightness, use 2 LEDs in parallel and adjust the resistor accordingly

---

## 🧰 Tools Used

- 🖥️ KiCad / EasyEDA (for schematic & PCB)
- 🔧 Soldering iron & basic tools
- 🧪 Multimeter (for circuit verification)

---

## 📄 License

This project is open-source under the [MIT License](../LICENSE).  
Feel free to modify, build upon, or use it in your own projects.

---

## 🙋‍♂️ Author & Credits

Designed by **Ruthvik Reddy A**  
For questions, reach out at: `reddy.ruthvik0411@gmail.com`

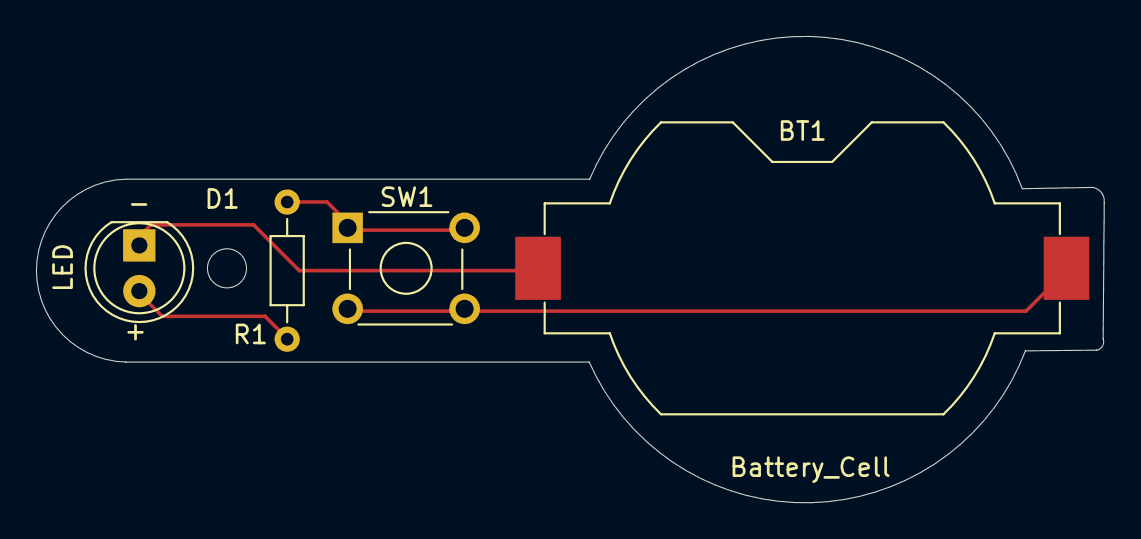
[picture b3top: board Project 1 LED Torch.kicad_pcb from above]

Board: 2 copper layers, 59.3 x 25.9 mm, 4 parts (0 on the bottom side), 4 nets.

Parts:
BT1: Battery_Cell; BatteryHolder_Keystone_1058_1x2032
D1: LED; LED_D5.0mm
R1: R1; R_Axial_DIN0204_L3.6mm_D1.6mm_P7.62mm_Horizontal
SW1: SW_DPDT_x2; SW_TH_Tactile_Omron_B3F-10xx

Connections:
/LED_Anode: D1.2 (A), R1.1
/LED_Cathode: BT1.2 (-), D1.1 (K)
/bat_pos: BT1.1 (+), SW1.2 (B)
unnamed: R1.2, SW1.1 (A)

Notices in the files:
README.md:
License: MIT
